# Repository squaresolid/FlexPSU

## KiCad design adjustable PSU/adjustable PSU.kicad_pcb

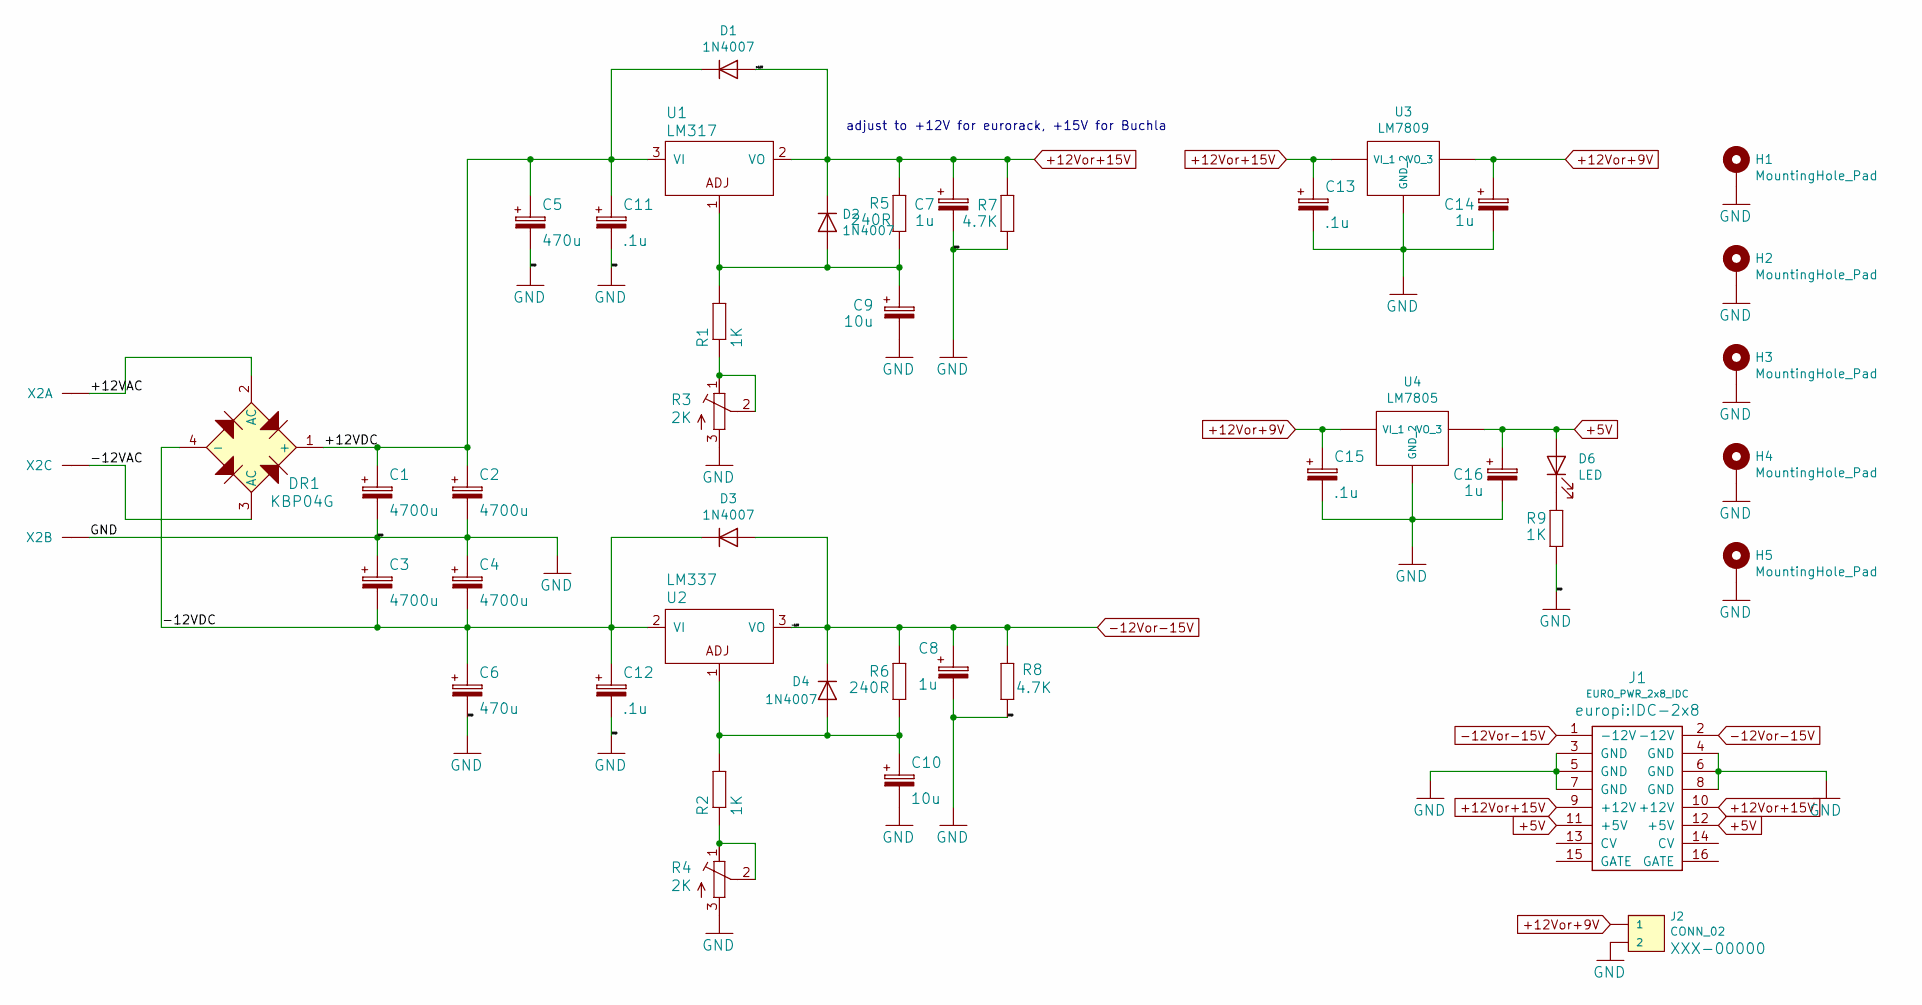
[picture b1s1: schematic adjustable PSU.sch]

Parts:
C1, C2, C3, C4: 4700u; C_POL-RADIAL-15MM
C5, C6: 470u; C_Radial_D8.0mm_H7.0mm_P3.50mm
C7, C8, C14, C16: 1u; C_Radial_D5.0mm_H5.0mm_P2.00mm
C9, C10: 10u; C_Radial_D5.0mm_H5.0mm_P2.00mm
C11, C12, C13, C15: .1u; CAP-PTH-5MM
D1, D2, D3, D4: 1N4007; DIODE-1N400X
D6: LED; LED_3MM
DR1: KBP04G; SIP-4_W3.81mm; MPN KBP04G; Digi-Key_PN KBP04G-ND
H1, H2, H3, H4, H5: MountingHole_Pad; MountingHolePad_M3
J1: EURO_PWR_2x8_IDC; IDC-2x8
J2: CONN_02; 1X02
R1, R2: 1K; R_AXIAL_0.5W
R3, R4: 2K; R-TRIMPOT64W
R5, R6: 240R; R_AXIAL_0.5W
R7, R8: 4.7K; R_AXIAL_0.5W
R9: 1K; R_AXIAL_0.25W
U1: LM317; TRANSISTOR_POWER_TO220-ADJ
U2: LM337; TRANSISTOR_POWER_TO220-ADJ
U3: LM7809; TO220-IGO
U4: LM7805; TO220-IGO
X2: 22-23-2031; SCREWTERMINAL-3.5MM-3

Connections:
+5V: C16.+, D6.2 (A), J1.11 (+5V), J1.12 (+5V), U4.3 (VO_3)
+12Vor+9V: C14.+, C15.+, J2.1, U3.3 (VO_3), U4.1 (VI_1)
+12Vor+15V: C7.+, C13.+, D1.2 (A), D2.1 (K), J1.9 (+12V), J1.10 (+12V), R5.2, R7.2, U1.2 (VO), U3.1 (VI_1)
-12Vor-15V: C8.+, D3.2 (A), D4.1 (K), J1.1 (-12V), J1.2 (-12V), R6.2, R8.2, U2.3 (VO)
/+12VAC: DR1.2 (AC), X2.1
/+12VDC: C1.+, C2.+, C5.+, C11.+, D1.1 (K), DR1.1 (+), U1.3 (VI)
/-12VAC: DR1.3 (AC), X2.3
/-12VDC: C3.-, C4.-, C6.+, C12.+, D3.1 (K), DR1.4 (-), U2.2 (VI)
GND: C1.-, C2.-, C3.+, C4.+, C5.-, C6.-, C7.-, C8.-, C9.-, C10.-, C11.-, C12.-, C13.-, C14.-, C15.-, C16.-, H1.1, H2.1, H3.1, H4.1, H5.1, J1.3 (GND), J1.4 (GND), J1.5 (GND), J1.6 (GND), J1.7 (GND), J1.8 (GND), J2.2, R3.3 (E), R4.3 (E), R7.1, R8.1, R9.1, U3.2 (GND_2), U4.2 (GND_2), X2.2
unnamed: C9.+, D2.2 (A), R1.2, R5.1, U1.1 (ADJ)
unnamed: C10.+, D4.2 (A), R2.2, R6.1, U2.1 (ADJ)
unnamed: D6.1 (K), R9.2
unnamed: R1.1, R3.1 (A), R3.2 (S)
unnamed: R2.1, R4.1 (A), R4.2 (S)

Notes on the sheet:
adjust to +12V for eurorack, +15V for Buchla

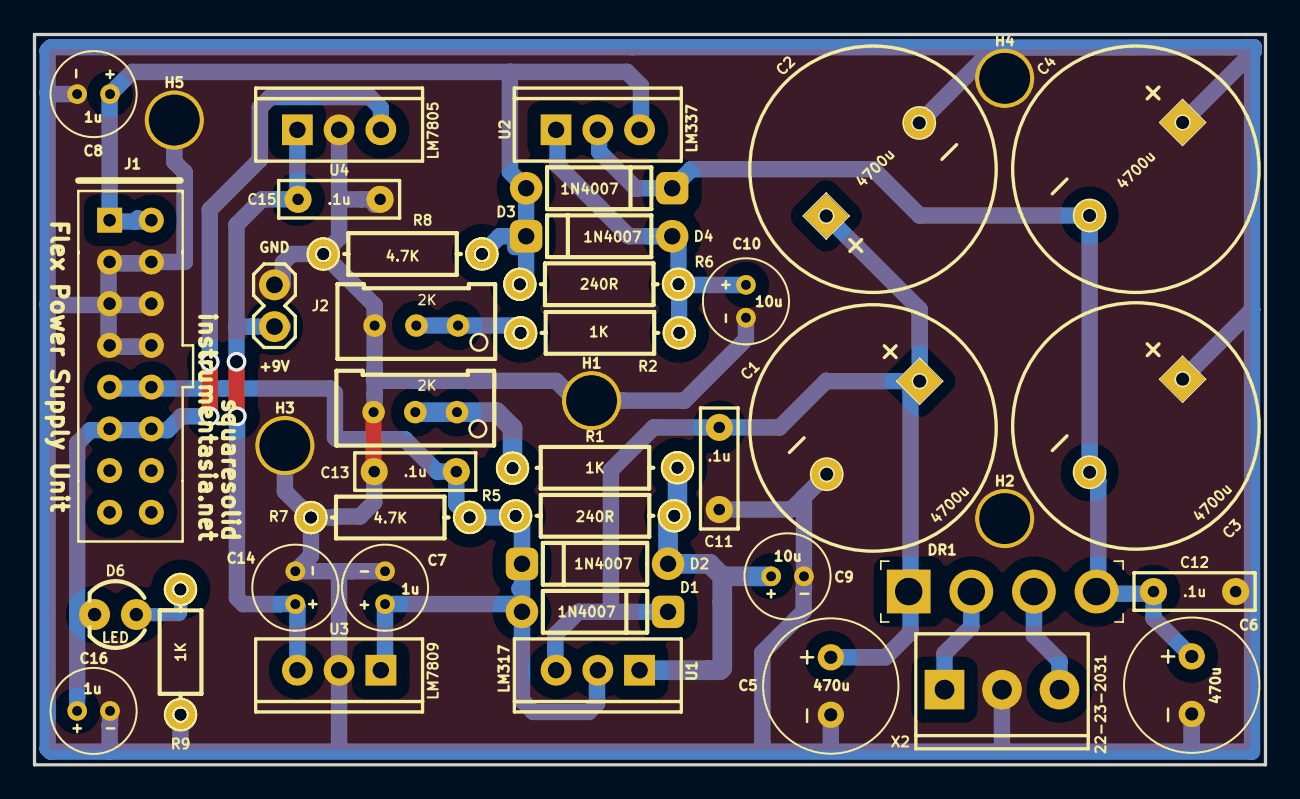
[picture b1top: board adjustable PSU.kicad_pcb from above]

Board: 2 copper layers, 74.9 x 44.4 mm, 43 parts (0 on the bottom side), 14 nets.

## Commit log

2022-02-04 Flexible Power Supply Unit PCB design for eurorack or Buchla System
